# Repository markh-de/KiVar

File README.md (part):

# KiVar − Multi-Scope PCB Assembly Variants for KiCad

KiVar is a tool for **KiCad PCB Assembly Variant and Micro-Variant selection**, provided as platform-independent

 * **KiCad Plugin** and
 * **Command Line Application**.

PCB component variation rules for multiple independent design scopes are defined in component (i.e. symbol or footprint) fields.  This allows for the complete low-level variation configuration to be contained in the schematic and board files without requiring external data outside the native KiCad design.

In addition, Variant Definition Tables (KiCad-independent CSV format) can optionally be used to summarize the configuration of these low-level scopes in classic flat variants, which can then be switched between.

> [!NOTE]
> While KiCad 10 introduces native assembly variant support, KiVar's concept of **multiple independent Aspects** (or _Micro-Variants_) goes beyond a single flat variant switch.  Each Aspect represents its own variation scope &ndash; such as LED current, boot source, I²C address, or output voltage &ndash; and each can be set independently or grouped into named Variants.  This multi-scope approach continues to offer unique flexibility that complements or exceeds what common EDA variants provide.

## Featured at KiCon Europe 2024

For a presentation of the **concepts** and **features** of KiVar, including a **short tutorial**, you can watch the talk ["**Managing PCB Assembly Variants with KiVar**"](https://youtu.be/SpXH380KWUA), which was recorded at KiCon Europe 2024 in Bochum, Germany.

The presentation **slides** including the embedded screencast videos can be downloaded from the [pretalx page](https://pretalx.kicad.org/kicon-europe-2024/talk/QMYVCL/).

> [!NOTE]
> The presentation covered KiVar 0.4.0, which did not yet support flat variants (added in 0.5.0).

Many thanks to Seth for the invitation.

## Features

KiVar assigns PCB component **values**, **field content**, **attributes** (such as _Do not populate_, _Not in position files_ or _Not in BoM_) and **features** (such as _individual 3D model visibility_ or _solder paste application_) according to variation rules specified in footprint fields.  When applying those rules, components are modified **in place**, allowing for immediate update of the PCB design as well as the 3D view and enabling compatibility with _any_ exporter.

Back-propagation of modified component data from the PCB to the schematic can be done in an extra step.

## What to Expect

### KiCad Plugin

Example selection dialog of the **KiVar Plugin for KiCad**:

### Command Line Interface Application

Example usage of the **KiVar Command Line Interface app**:

```
$ kivar list --selection kivar-demo.kicad_pcb 
~: 'Series 1000' 'Series 3000 Basic' ['Series 3000 Pro'] 'Series 5000 Basic' 'Series 5000 Pro'
BOOT_SRC~: EMMC JP NAND [SD]
IOEXP_TYPE/ADDR~: 9535/0x20 [9535/0x24] 9539/0x74
EEPROM_ADDR~: [0x54] 0x55
I_LED_MA~: 10 20 30 40 50 60 70 80 90 [100] 110 120 130 140 150 JP
ISL91127~: [IRAZ] IRNZ
UVLO_LO/HI: 2.41V/3.40V [3.15V/3.57V]
VOUT: 1.2V [1.8V] 2.5V 3.3V

$ kivar set --variant 'Series 5000 Pro' --verbose kivar-demo.kicad_pcb 
Changes (19):
    Change R1 'Do not populate' from 'true' to 'false' (EEPROM_ADDR=0x55).
    Change R1 'Exclude from bill of materials' from 'true' to 'false' (EEPROM_ADDR=0x55).
    Change R1 'Exclude from position files' from 'true' to 'false' (EEPROM_ADDR=0x55).
    Change R2 'Do not populate' from 'false' to 'true' (EEPROM_ADDR=0x55).
    Change R2 'Exclude from bill of materials' from 'false' to 'true' (EEPROM_ADDR=0x55).
    Change R2 'Exclude from position files' from 'false' to 'true' (EEPROM_ADDR=0x55).
    Change R21 field 'VarID' from 'A' to 'B' (I_LED_MA=110).
    Change R30 'Do not populate' from 'true' to 'false' (I_LED_MA=110).
    Change R30 'Exclude from bill of materials' from 'true' to 'false' (I_LED_MA=110).
    Change R30 'Exclude from position files' from 'true' to 'false' (I_LED_MA=110).
    Change U1 field 'I2C Address' from '0x54' to '0x55' (EEPROM_ADDR=0x55).
    Change U1 field 'VarID' from '54' to '55' (EEPROM_ADDR=0x55).
    Change U4 value from 'TCA9535PWR' to 'TCA9539PWR' (IOEXP_TYPE/ADDR=9539/0x74).
    Change U4 visibility of 3D model #1 from 'true' to 'false' (IOEXP_TYPE/ADDR=9539/0x74).
    Change U4 visibility of 3D model #2 from 'false' to 'true' (IOEXP_TYPE/ADDR=9539/0x74).
    Change U4 field 'I2C Address' from '0x24' to '0x74' (IOEXP_TYPE/ADDR=9539/0x74).
    Change U4 field 'VarID' from '24' to '74' (IOEXP_TYPE/ADDR=9539/0x74).
    Change U4 field 'Datasheet' from 'http://www.ti.com/lit/ds/symlink/tca9535.pdf' to 'http://www.ti.com/lit/ds/symlink/tca9539.pdf' (IOEXP_TYPE/ADDR=9539/0x74).
    Change U4 field 'MPN' from 'TCA9535PWR' to 'TCA9539PWR' (IOEXP_TYPE/ADDR=9539/0x74).
Board saved to file "kivar-demo.kicad_pcb".

$ kivar list --selection kivar-demo.kicad_pcb 
~: 'Series 1000' 'Series 3000 Basic' 'Series 3000 Pro' 'Series 5000 Basic' ['Series 5000 Pro']
BOOT_SRC~: EMMC JP NAND [SD]
IOEXP_TYPE/ADDR~: 9535/0x20 9535/0x24 [9539/0x74]
EEPROM_ADDR~: 0x54 [0x55]
I_LED_MA~: 10 20 30 40 50 60 70 80 90 100 [110] 120 130 140 150 JP
ISL91127~: [IRAZ] IRNZ
UVLO_LO/HI: 2.41V/3.40V [3.15V/3.57V]
VOUT: 1.2V [1.8V] 2.5V 3.3V

$ kivar check kivar-demo.kicad_pcb 
Check passed.  Matching variant and choices found for complete set of 7 aspect(s).

$ kivar state --query EEPROM_ADDR --query BOOT_SRC kivar-demo.kicad_pcb 
0x55
SD
```

The KiVar CLI application provides support for

 * setting,
 * querying,
 * listing and
 * analyzing

low-level and high-level variant data and current settings of a PCB.  It can also be used in Continuous Integration services.

## Concepts

Key concepts of KiVar are:

 * Designs may contain **multiple** independent **aspect scopes** (micro-variants).
 * Variation rules are **fully contained** in component fields of native design files (no external configuration files involved) and **portable** (i.e. copying components to another design keeps their variation specification intact).
 * Component values, fields, attributes and features are modified **in place** with immediate effect, enabling compatibility with all exporters that work on the actual component data.
 * **No external state information** is stored; currently matching variation choices are detected automatically.
 * Optional external **variant** definition table in independent file format (CSV) enables switching of aspect groups based on a single variant name.

## Supported KiCad Versions

KiCad Release Series | Compatible KiVar Releases
-------------------- | -------------------------
7.x                  | 0.0.1 &ndash; 0.1.2
8.x                  | 0.2.0 &ndash; _latest_
9.x                  | 0.4.2 &ndash; _latest_
10.x                 | 0.5.4 &ndash; _latest_

> [!NOTE]
> KiCad 10 introduces native assembly variant support.  However, KiVar's **multi-scope Aspect model** provides flexibility beyond KiCad's built-in single design-scope variant selection.

KiVar currently (still) uses the SWIG-based Python bindings of pcbnew (KiCad PCB Editor).

## Installation

> [!NOTE]
> The KiCad Plugin and the CLI app can be installed independently of each other.  As the KiCad Plugin does not have external module dependencies, it does not require the CLI package to be installed.

### KiVar Plugin

The recommended plugin installation method is to use KiCad's integrated **Plugin and Content Manager**.  KiVar is included in the **official PCM repository**, allowing a smooth and safe installation and update experience.

Required steps:

1. Start the _Plugin and Content Manager_ from the KiCad main window.
2. Find _KiVar_ in the **Plugins** section.
3. Mark it for installation and apply the pending changes.
4. The _KiVar_ plugin icon should now appear in the PCB Editor (pcbnew) toolbar.

### KiVar Command Line Application

To install the latest KiVar CLI app directly from the official **KiVar PyPI repository**, follow the instructions below depending on your operating system.

#### Installation on Linux

For conveniently installing the KiVar CLI app inside a dedicated Virtual Environment, it is recommended to use `pipx`.  Install it, if required, depending on your type of Linux distribution.  With `pipx` in place, open a shell and run:

```
pipx install --system-site-packages kivar
```

This will install the KiVar CLI app in a location available in your search path.  The name of the executable is `kivar`.

To check that the installation was successful and that the correct `pcbnew` module version is used, run:

```
kivar --version
```

#### Installation on Windows

On Windows systems, KiCad ships with its own Python distribution included.  It is important to **use the KiCad-provided Python interpreter** for installing the KiVar CLI app.

To install the `kivar.exe` executable, open a `cmd.exe` shell and run:

```
"%ProgramFiles%\KiCad\9.0\bin\python.exe" -m pip install --user kivar
```

> [!NOTE]
> The above command assumes that KiCad version 9.0 is used.  Please adapt the version part (`9.0`) of the command, if required.

If you don't happen to have the app installation directory already listed in your `PATH` variable, then `pip` will print a warning including the actual installation directory:

```
WARNING: The script kivar.exe is installed in '...' which is not on PATH.
```

This message includes the location of the directory in which the `kivar.exe` executable is installed.

You will need to run `kivar` from this exact location.  If desired, you can add the installation directory to your `PATH` variable (as suggested by `pip`), or use any other preferred method of making the executable callable from any working directory.

To check that the installation was successful and that the correct `pcbnew` module version is used, run:

```
"%USERPROFILE%\Documents\KiCad\9.0\3rdparty\Python311\Scripts\kivar" --version
```

> [!NOTE]
> The path used in the above command may differ on your system.  If in doubt, use the directory printed in the `pip` installation warning.  If no such warning appeared, you might be able to simply use `kivar --version` (without path specifier).

#### Installation on macOS

On macOS systems, KiCad ships with its own Python distribution included.  It is important to **use the KiCad-provided Python interpreter** for installing the KiVar CLI app.

To install the `kivar` executable, open a shell and run:

```
"/Applications/KiCad/KiCad.app/Contents/Frameworks/Python.framework/Versions/Current/bin/python3" -m pip install --user kivar
```

If you don't happen to have the app installation directory already listed in your `PATH` variable, then `pip` will print a warning including the actual installation directory:

```
WARNING: The script kivar is installed in '...' which is not on PATH.
```

To be able to call `kivar` from _any_ working directory without using the executable's full path, run the following commands to create a symlink in your `~/.local/bin` directory (which should be part of `PATH`).  The actual Python version part (`3.9` here) may vary, depending on the KiCad-included Python version.

```
mkdir -p "$HOME/.local/bin"
ln -s "$HOME/Library/Python/3.9/bin/kivar" "$HOME/.local/bin/kivar"
```

> [!NOTE]
> The path used in the above command may differ on your system.  If in doubt, use the directory printed in the `pip` installation warning.

To check that the installation was successful and that the correct `pcbnew` module version is used, run:

```
kivar --version
```

## Usage

> [!TIP]
> This manual may seem very formal and complicated, especially to new users.  To get a first impression how KiVar works, it is highly recommended to watch the live presentation ["**Managing PCB Assembly Variants with KiVar**"](https://youtu.be/SpXH380KWUA) and have a look at the **[usage examples](#usage-examples)** as well as the **[demo project](demo/)** (from which the examples are taken).

> [!IMPORTANT]
> This manual refers to the **0.5.x** series of KiVar.  If you are still using an older version, please consider [updating](#installation) KiVar and [migrating](#migrate) your variation rules.

The process of writing and assigning rules to components (i.e. symbols and footprints) is done manually using simple text expressions.

In addition, groups of configurations can be conveniently managed in tables (CSV files).

Once all relevant components are equipped with their variation rules and variant tables are set up (optionally), KiVar allows the selection of variation choices using either an easy-to-use dialog interface (when using the KiCad Plugin) or a command-line interface (when using the CLI app) and takes care of the automatic analysis and assignment of the corresponding component values, fields, attributes and features.

The following sections describe the process of configuring your schematic or board, your variant table (if desired) and &ndash; after that &ndash; selecting a variation configuration from the previously configured variation choices.  Examples are provided where appropriate.

### Component Variation Setup

While it is recommended to define variation rules in the schematic (i.e. in symbol fields) and propagate them to the board, it is also possible to define those rules directly in the board (i.e. in footprint fields) and propagate them back to the schematic.  Either way, in order for KiVar to utilize the variation rules, they must be present in the footprint fields, as KiVar uses the _pcbnew_ API wrapper and can therefore only operate on the board (not schematic) data, which must then be [propagated back to the schematic](#updating-the-schematic).

> [!TIP]
> If you are already experienced with writing variation rules for **older KiVar versions**, it is highly recommended to read the **[KiVar Migration Guide](#migrate)**, which covers the most important changes introduced with newer KiVar releases.

#### Definition of Terms

Whenever specific terms appear capitalized in this document, the following definitions apply:

 * **Aspect:**  
   A scope (or dimension) of variation changes, which are defined by _Choices_ (see below).  One PCB design can refer to multiple Aspects.  Each component that makes use of KiVar variations must refer to _exactly one_ [Aspect Identifier](#aspect-identifier).  
   For example, an Aspect can be the I²C address of an EEPROM IC, using an identifier such as `EEPROM_I2C_ADDR`.
 
 * **Choice:**  
   A state of an _Aspect_.  Defined with a set of [Content](#content-specifiers) (component values or component field values) and/or [Properties](#property-specifiers) to be assigned to specific components.  A Choice is _always_ related to a specific _Aspect_ and only valid in its context.  
   For example, possible Choices for the I²C address Aspect could be `0x50`, `0x51`, `0x52`, `0x53`.

 * **Configuration:**  
   A fully defined selection of _specific_ _Choices_ for _all_ available _Aspects_.  In other words, one specific board assembly variant state.  
   An example is shown in the following section.

 * **Record:**  
   An entry in a KiVar-specific custom field of a component (symbol or footprint) to be interpreted by the KiVar rule processor.

 * **Assignment:**  
   A group of one or more Records containing [Choice Expressions](#choice-expressions) to assign a set of data to the same Assignment target (e.g. the [component itself](#component-scope), or an existing [custom field of the component](#field-scope)).

 * **Variant:**  
   A set of _Choices_ applying to a selected set of _Aspects_ (so-called _Bound Aspects_ &ndash; in contrast to _Free Aspects_, which can be modified independently of the selected Variant).  
   The use of Variants is optional.  If used, Variants are [configured independently](#top-level-variants) "on top" of the existing _Aspect_ configuration.

#### Variants

##### Multi-Scope Concept

A central point of KiVar's concepts is that one design can use any number of **independent** Aspect scopes and each scope can be switched to a specific Choice (Aspect state).

This is KiVar's key differentiator from classic flat variant systems &ndash; including KiCad 10's native variant support.  Instead of a single monolithic variant switch that controls all component changes at once, KiVar treats each variation dimension (e.g. output voltage, boot source, LED current, I²C address) as its own independently switchable **Aspect**.  Each Aspect has its own set of **Choices** (Micro-Variants), which can be selected freely and in any combination.  This makes it possible to represent a much larger configuration space with far fewer explicitly defined Variants.

##### Flat Variants

Most EDA tools offer a "flat variant" model.  Which makes sense, because in real-world projects, it is often desired to have a **single global** (i.e. top-level) switch to choose between assembly options, for example to switch between product models or revisions that always combine a specific set of assembly Choices.

##### Mixed Approach

KiVar uses a mixed approach, combining the benefits of both concepts:

The definition of Variants makes it possible to work with a single switch, while the configuration of the individual Variants is still very convenient, as it is only necessary to **switch between Choices for Bound Aspects, not between the full set of component values and attribute data**.  This additional layer of abstraction keeps Variant definitions very simple and readable.

In addition to a single Variant switch, KiVar also allows having so-called _Free Aspects_, i.e. scopes that are not modified when selecting a specific Variant.  So even after switching the main Variant, it is still possible to have a few independent switches for further assembly options, if desired.

##### Division of Resposibilities

Component value and attributes are configured in _low-level_ Aspect definitions directly in the native KiCad design files, while _top-level_ Variants are configured independently in an external table.

This makes it possible to divide the administration of each of these parts between different departments or editors, providing a _development_ and _management_ view:

While low-level Aspects can be defined by the KiCad hardware _developers_ during design, the project _manager_ can be in charge of defining model/series/product feature configurations by mapping Aspect Choices to specific Variants.  For the _management_ view, it is not even required to use an installation of KiCad (or KiVar).  A simple spreadsheet editor is sufficient to manage the Variants table.

##### Specification

Details about the specification of Variants can be found later in this manual in the [Top-Level Variants section](#top-level-variants).

#### Relation of Aspects and Choices

Each component that uses KiVar variation rules must bind to _exactly one_ variation **Aspect** to which all specified variation **Choices** for that component will then relate to.

> [!IMPORTANT]
> There may exist _multiple_ Aspects per design, and for each Aspect there may exist _multiple_ Choices.  
> One component must relate to a _single_ Aspect, but may relate to an _unlimited number_ of Choices for that Aspect.  
> Multiple components may (and usually will) refer to the same Aspects and Choices.

_Example:_

 * Design
   * Aspect `EEPROM_I2C_ADDR`
     * Choice `0x50`
     * Choice `0x51`
     * Choice `0x52`
     * Choice `0x53`
  
   * Aspect `BOOT_SRC`
     * Choice `EMMC`
     * Choice `SDCARD`
     * Choice `NAND`
  
   * Aspect `VIO_LEVEL`
     * Choice `1.8V`
     * Choice `2.5V`
     * Choice `3.3V`

One possible resulting example _Configuration_ for this design:

`EEPROM_I2C_ADDR=0x52 BOOT_SRC=NAND VIO_LEVEL=1.8V`

KiVar computes possible sets of Aspect and Choice definitions internally by checking each component's field data for KiVar [Records](#records) and the [Assignments](#assignments) resulting from them.  The structure and syntax of the expressions used in such Records are described in the following sections.

#### Overriding KiVar Record Keywords

By default, KiVar uses the keywords `Var` and `Aspect` in component fields to identify variation rules and Aspect Identifiers.

**You can override these default keywords** by defining the KiCad project text variables `KIVAR_KEYWORD_VAR` and `KIVAR_KEYWORD_ASPECT`, respectively.

For example, to use `Scope` instead of `Aspect`, set `KIVAR_KEYWORD_ASPECT` = `Scope` in your project's text variables.

This allows you to adapt KiVar to your own naming conventions or to avoid conflicts with other tools.  However, using custom keywords may make your variation rules less portable.

#### Records

The text expressions that describe the variation rules are noted as **Record**s, i.e. as custom field entries with each field's name containing the keyword `Var` in one of [several forms](#record-formats).

Records must appear in the component they relate to.

A usual Record contains the following elements:

 * [Assignment](#assignments) Target information: _implicit, depending on the [Assignment Scope](#assignment-scopes)_
 * [Choice Expression(s)](#choice-expressions): _one or more, depending on the [Record Format](#record-formats)_
   * [Choice Identifier List](#choice-identifier-lists): _list of affected Choice names_
   * [Choice Argument(s)](#choice-arguments): _data to be assigned to the affected Choices_
     * [Content Specifier(s)](#content-specifiers): _provide data to be used as component value or custom field value_
     * [Property Specifier(s)](#property-specifiers): _provide settings to switch component attributes or footprint features_

There is a special Aspect Specifier Record type, discussed in the [corresponding section](#aspect-identifier).

Records can use various notations, depending on their [Format](#record-formats).  Details are described in the following sections.

> [!NOTE]
> The default field keywords `Var` and `Aspect` can be changed per project.  
> See [Overriding KiVar Record Keywords](#overriding-kivar-record-keywords) for details.

#### Assignments

Each Record addresses a specific target that the contained rule expressions refer to.  A group of one or more Records with the same target form an **Assignment**.

Possibe Assignment targets are:

 * the component's **value**,
 * one of the component's (custom) **fields**,
 * a component **attribute** and/or
 * a component **feature** (e.g. solder paste application, 3D representation).

#### Choice Expressions

Depending on the used [Format](#record-formats), each Record can carry either a single or multiple **Choice Expression**s.

Each Choice Expression specifies

 * for which [Choice Identifiers](#choice-identifiers) to assign
 * which data to the Record's [Assignment](#assignments) target.

For each Choice Expression, this data is passed via the

 * [Choice Identifier List](#choice-identifier-lists) and
 * [Choice Arguments](#choice-arguments).

#### Choice Arguments

The actual data to be assigned to the Choices passed as [Choice Identifier List](#choice-identifier-lists) is expressed in the **Choice Argument**s.

These Choice Arguments are a list of _space_-separated specifiers used to declare the data to be assigned to the [Assignment](#assignments) Target.

Each _Choice Argument_ inside the _Choice Argument List_ can be of one of two possible types:

 * a [**Content** Specifier](#content-specifiers) to assign a component _value_ or a specific _custom field value_, or
 * a [**Property** Specifier](#property-specifiers), e.g. to mark a component _(un)fitted_, _(not) in BoM_, _(not) in position files_ or change a dedicated footprint feature.

Argument types are distinguished by their **first (unescaped) character** and will be explained in more detail in the following sub-sections.

##### Content Specifiers

###### Purpose

One or more **Content Specifiers** can be used to form a string to be assigned to the component value or to any component custom field (such as _Manufacturer_, _MPN_, ...).

###### Syntax

Each argument beginning with a character _other than_ `-` and `+` is interpreted as a **Content Specifier**.

There may exist multiple Content Specifiers in each [Choice Argument](#choice-arguments) List.  Their values will be concatenated with one ` ` (space) character as separator to form the resulting Content string.  However, each [Assignment](#assignments) may have a maximum of _one_ resulting Content specified.  For example: `Choice1("hello world"   foo bar)` will result in `Choice1` to be assigned the content `hello world foo bar`, but multiple Content Assignments to the same [Choice Identifier](#choice-identifiers), such as `Choice1("hello world") Choice1(foo bar)`, are invalid.  This restriction is due to the fact that [Records](#records) can be provided in different [Formats](#record-formats) and there is no guaranteed processing (concatenation) order.

###### Evaluation

All Content Specifiers inside the Choice Arguments are evaluated from left to right and concatenated with one space character between each argument to form the final content string to be assigned when the corresponding Choice is selected.

> [!NOTE]
> As arguments can be separated by _any_ number of space characters, each separation will result in a single space character in the final content, no matter how many spaces were used for the argument separation originally (similar to HTML).  For strings that shall be assigned in a verbatim way (such as a URL), it is highly recommended to use [quoting techniques](#quoting-and-escaping).

###### Examples

The Content Specifiers in the following input Choice Argument Lists will result in the following Content strings:

Choice Argument List input | Resulting Content string | Explanation
-------------------------- | ------------------------ | -----------
`100nF`                    | `100nF`                  | Simple single arguments can be noted without [escaping or quoting](#quoting-and-escaping) as long as they don't contain certain special characters (discussed later).
`470µF 10%`                | `470µF 10%`              | Uncritical text, no verbatim adoption of the arguments required.
`470µF   10%`              | `470µF 10%`              | Multiple separator characters will be converted to a single separator. As the text is uncritical, this conversion may even be desired.
`'https://kivar.markh.de/ds/abc123.pdf'` | `https://kivar.markh.de/ds/abc123.pdf` | Strings to be used verbatim should always be enclosed in [quote](#quoting-and-escaping) characters.
`'abc   def ' 123   456`   | `abc   def  123 456`     | Mixed type of quoted and unquoted representation.  Note how the trailing space after `def` remains contained in the result.
`abc "def 'ghi' jkl" mno`  | `abc def 'ghi' jkl mno`  | Outer double quotes encapsulate inner single quotes, which are part of the verbatim string.
`abc 'def "ghi" jkl' mno`  | `abc def "ghi" jkl mno`  | Outer single quotes encapsulate inner double quotes, which are part of the verbatim string.
`abc \d\e\f\ \ ghi\'jkl\\mno` | `abc def  ghi'jkl\mno` | [Escaping](#quoting-and-escaping) (prepending a backslash) ensures that the following character is interpreted verbatim, not as a special character.  To create a backslash (the escape character) string, use a double backslash (i.e. escape the backslash).
`\+10% \-5% \-12V \+5V`    | `+10% -5% -12V +5V`      | If the first character of a Content Specifier is a `-` or `+`, the corresponding Choice Argument must be prepended with a backslash (`\`) character or be part of a verbatim string (see next example).
`"+10%" '-5%' "-"12V '+'5V` | `+10% -5% -12V +5V`     | If the first character of a Content Specifier is a `-` or `+`, the corresponding Choice Argument must be part of a verbatim string or be prepended with a backslash (`\`) character (see previous example).

##### Property Specifiers

###### Purpose

KiVar provides a set of boolean component _Properties_ that allow controlling the component attributes

 * **Do not Populate**,
 * **Not in Position Files**, and
 * **Not in BoM**
 
as well as component features, such as

 * **Individual 3D Model Visibility** and
 * **Solder Paste Application**.

###### Syntax

Each argument beginning with a `-` or `+` is interpreted as a **Property Specifier**, which is a combination of **Property Modifiers** and **Property Identifiers**.

Each Property Specifier must start with a _Property Modifier_, defining the boolean state (_true_ or _false_, represented by `+` or `-`, respectively) to be assigned to the Properties subsequently specified by their corresponding _Property Identifiers_.

###### Evaluation

All Property Specifiers inside a [Choice Argument List](#choice-arguments) are evaluated from left to right, resulting in a set of defined boolean Property states for the corresponding component and Choice.  Properties _not_ defined in _any_ of the component's Choices are kept in their original state.

###### Attribute Properties

The following Properties allow modification of component _attributes_:

 * **Fit** (Property identifier `f`).  
   This Property specifies whether a component shall be fitted (Property state _true_) or unfitted (Property state _false_).  This Property is linked to the pcbnew footprint attribute _Do not populate_ with inverted polarity.
 * **Pos** (Property identifier `p`).  
   This Property specifies whether a component shall be included in the component placement/position files (Property state _true_) or excluded (Property state _false_).  This Property is linked to the pcbnew footprint attribute _Not in Position Files_ with inverted polarity.
 * **Bom** (Property identifier `b`).  
   This Property specifies whether a component shall be included in the Bill of Materials (Property state _true_) or excluded (Property state _false_).  This Property is linked to the pcbnew footprint attribute _Not in BoM_ with inverted polarity.

###### Feature Properties

Additionally, the following Properties allow controlling footprint _features_:

 * **Model** (Property identifier `mN`, with `N` being an integer number).  
   This Property controls the visibility of each individual 3D model of the corresponding component footprint to either visible (Property state _true_) or invisible (Property state _false_).  An integer number must be provided directly following the first character of the Property identifier, representing the index of the model to be shown or hidden.  The index starts at 1.
 * **Solder** (Property identifier `s`).  
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
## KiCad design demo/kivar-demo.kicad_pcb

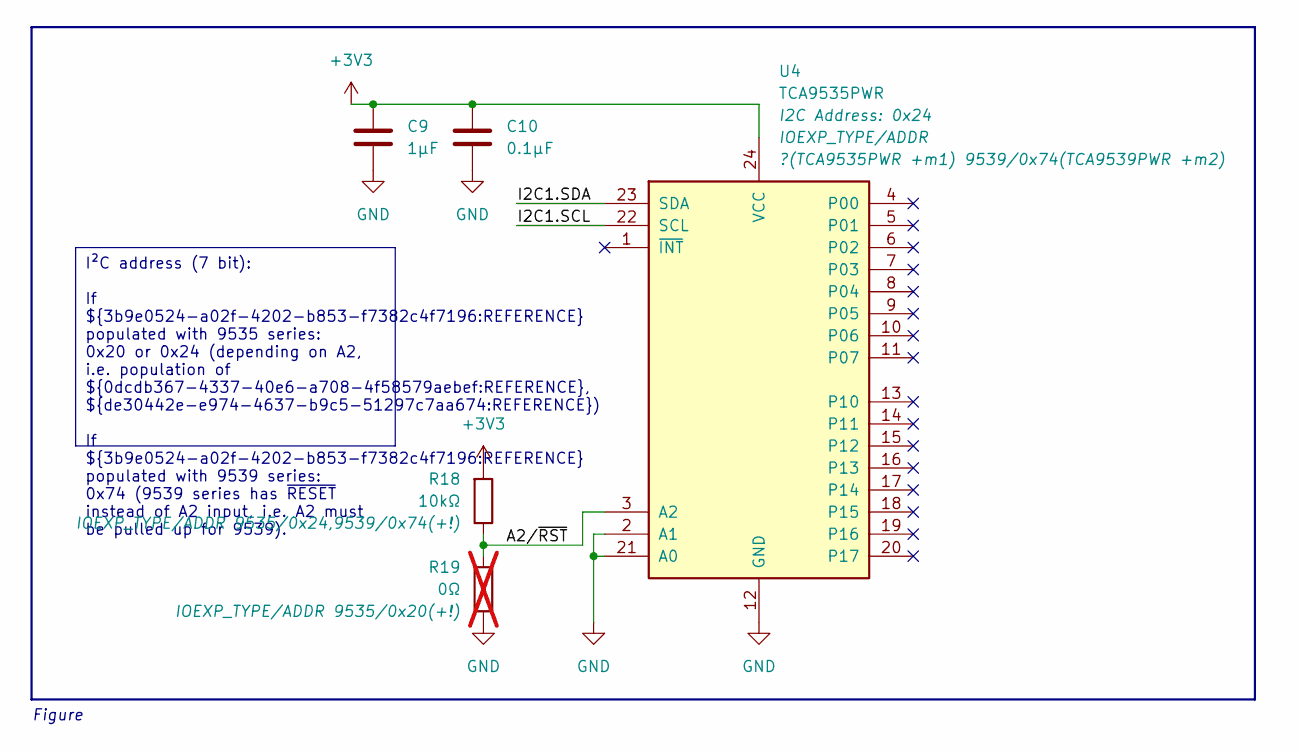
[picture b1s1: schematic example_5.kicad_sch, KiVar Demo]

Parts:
C9: 1µF; C_0603_1608Metric
C10: 0.1µF; C_0402_1005Metric
R18: 10kΩ; R_0402_1005Metric
R19: 0Ω; R_0402_1005Metric; not fitted
U4: TCA9535PWR; TSSOP-24_4.4x7.8mm_P0.65mm; MPN TCA9535PWR

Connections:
+3V3: C9.1, C10.1, R18.2, U4.24 (VCC); also elsewhere on the board
/Example 5: IC Type and Address Selection/A2/~RST: R18.1, R19.2, U4.3 (A2)
/Example 5: IC Type and Address Selection/I2C1.SCL: U4.22 (SCL)
/Example 5: IC Type and Address Selection/I2C1.SDA: U4.23 (SDA)
GND: C9.2, C10.2, R19.1, U4.2 (A1), U4.12 (GND), U4.21 (A0); also elsewhere on the board

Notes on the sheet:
I²C address (7 bit): If ${3b9e0524-a02f-4202-b853-f7382c4f7196:REFERENCE} populated with 9535 series: 0x20 or 0x24 (depending on A2, i.e. population of ${0dcdb367-4337-40e6-a708-4f58579aebef:REFERENCE}, ${de30442e-e974-4637-b9c5-51297c7aa674:REFERENCE}) If ${3b9e0524-a02f-4202-b853-f7382c4f7196:REF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
Figure

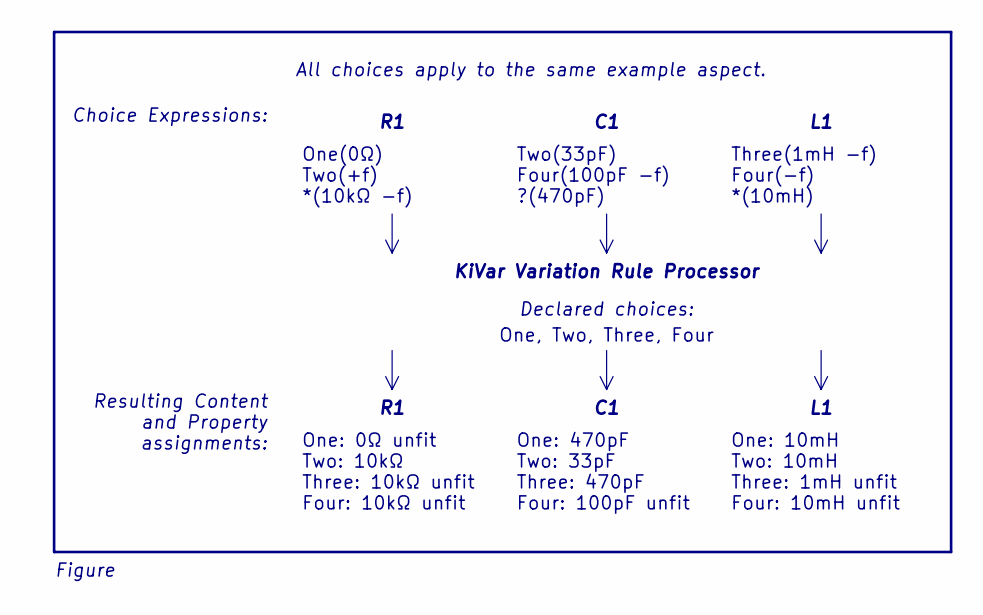
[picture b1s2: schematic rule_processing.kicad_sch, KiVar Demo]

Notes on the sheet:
KiVar Variation Rule Processor
One: 10mH Two: 10mH Three: 1mH unfit Four: 10mH unfit
Two(33pF) Four(100pF -f) ?(470pF)
One: 470pF Two: 33pF Three: 470pF Four: 100pF unfit
Three(1mH -f) Four(-f) *(10mH)
Figure
One, Two, Three, Four
One: 0Ω unfit Two: 10kΩ Three: 10kΩ unfit Four: 10kΩ unfit
All choices apply to the same example aspect.
Resulting Content and Property assignments:
Choice Expressions:
One(0Ω) Two(+f) *(10kΩ -f)
Declared choices:

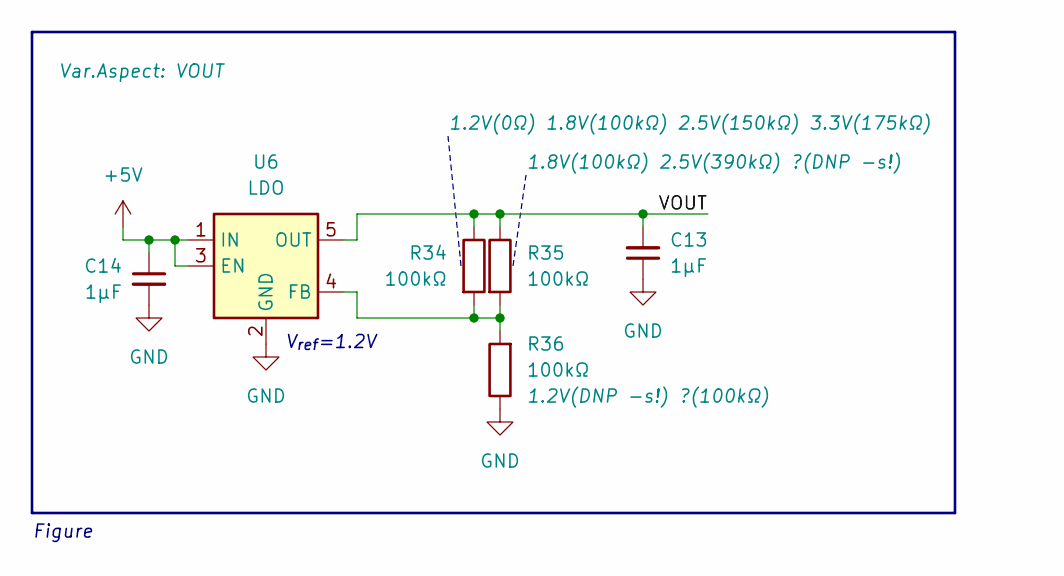
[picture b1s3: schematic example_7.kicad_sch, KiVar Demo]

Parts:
C13, C14: 1µF; C_0603_1608Metric
R34, R35, R36: 100kΩ; R_0402_1005Metric_Pad0.72x0.64mm_HandSolder
U6: LDO; SOT-23-5

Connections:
+5V: C14.1, U6.1 (IN), U6.3 (EN)
/Example 7: LDO Output Voltage Selection/VOUT: C13.2, R34.1, R35.1, U6.5 (OUT)
GND: C13.1, C14.2, R36.1, U6.2 (GND); also elsewhere on the board
unnamed: R34.2, R35.2, R36.2, U6.4 (FB)

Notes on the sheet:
V_{ref}=1.2V
Figure

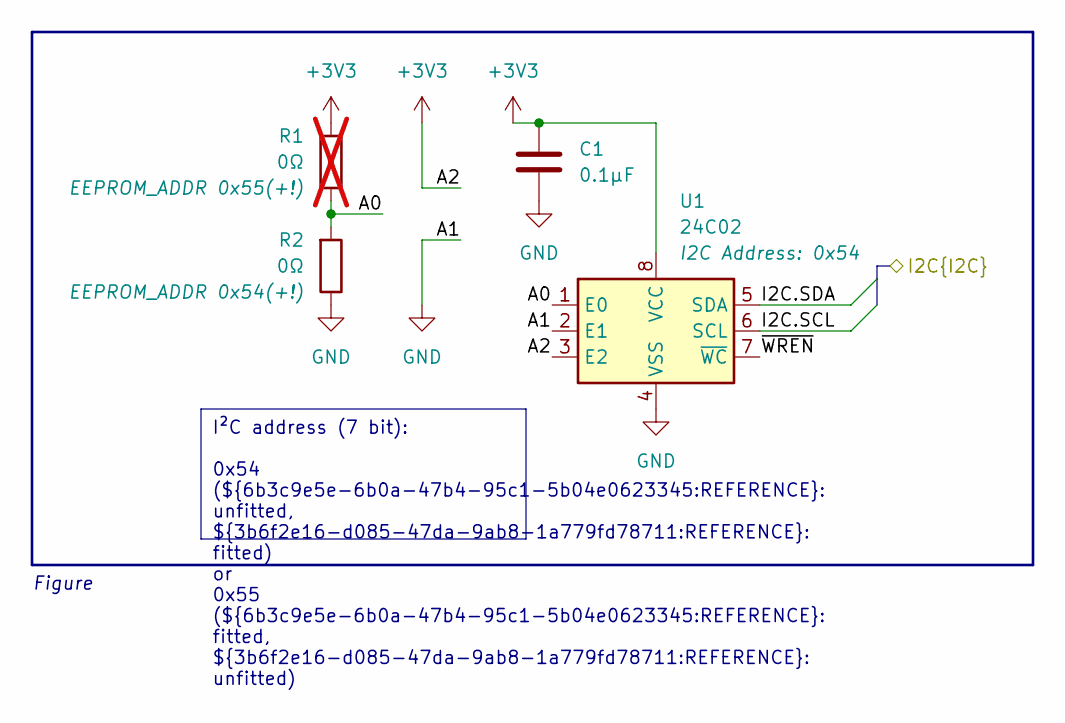
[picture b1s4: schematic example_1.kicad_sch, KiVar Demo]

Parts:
C1: 0.1µF; C_0402_1005Metric
R1: 0Ω; R_0402_1005Metric; not fitted
R2: 0Ω; R_0402_1005Metric
U1: 24C02; TSSOP-8_4.4x3mm_P0.65mm

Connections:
+3V3: C1.1, R1.2, U1.3 (E2), U1.8 (VCC); also elsewhere on the board
/Example 1: I²C Device Address Selection/A0: R1.1, R2.2, U1.1 (E0)
/Example 1: I²C Device Address Selection/I2C.SCL: U1.6 (SCL)
/Example 1: I²C Device Address Selection/I2C.SDA: U1.5 (SDA)
/Example 1: I²C Device Address Selection/~WREN: U1.7 (~WC)
GND: C1.2, R2.1, U1.2 (E1), U1.4 (VSS); also elsewhere on the board

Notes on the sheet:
I²C address (7 bit): 0x54 (${6b3c9e5e-6b0a-47b4-95c1-5b04e0623345:REFERENCE}: unfitted, ${3b6f2e16-d085-47da-9ab8-1a779fd78711:REFERENCE}: fitted) or 0x55 (${6b3c9e5e-6b0a-47b4-95c1-5b04e0623345:REFERENCE}: fitted, ${3b6f2e16-d085-47da-9ab8-1a779fd78711:REFERENCE}: unfitted)
Figure

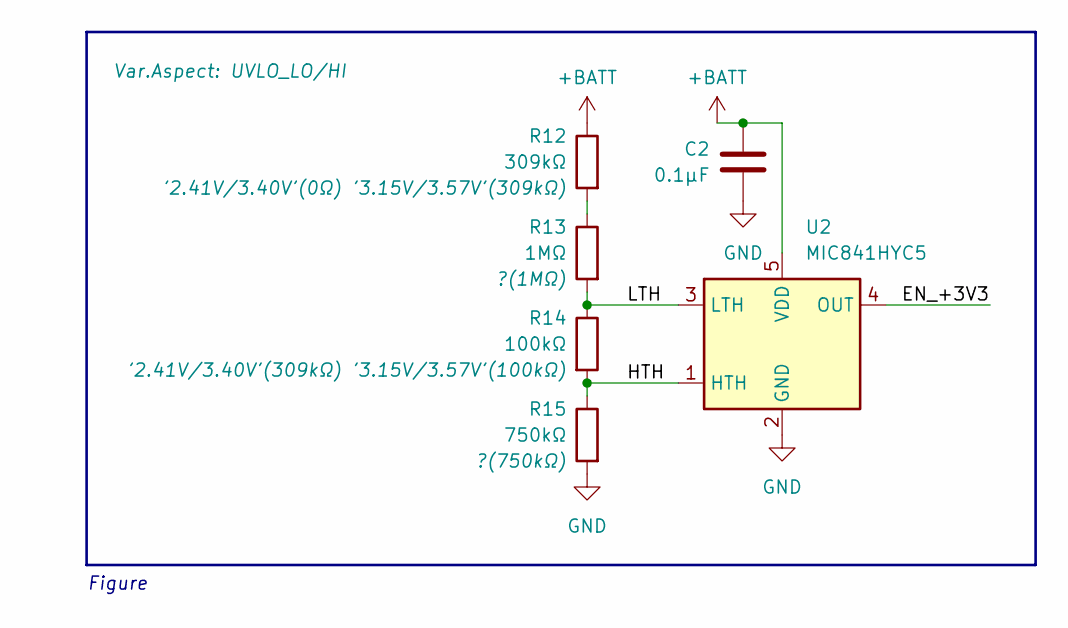
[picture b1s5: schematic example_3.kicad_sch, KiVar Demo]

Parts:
C2: 0.1µF; C_0402_1005Metric
R12: 309kΩ; R_0402_1005Metric
R13: 1MΩ; R_0402_1005Metric
R14: 100kΩ; R_0402_1005Metric
R15: 750kΩ; R_0402_1005Metric
U2: MIC841HYC5; SOT-353_SC-70-5

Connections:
+BATT: C2.1, R12.1, U2.5 (VDD); also elsewhere on the board
/Example 3: Undervoltage Trip Points/EN_+3V3: U2.4 (OUT)
/Example 3: Undervoltage Trip Points/HTH: R14.2, R15.1, U2.1 (HTH)
/Example 3: Undervoltage Trip Points/LTH: R13.2, R14.1, U2.3 (LTH)
GND: C2.2, R15.2, U2.2 (GND); also elsewhere on the board
unnamed: R12.2, R13.1

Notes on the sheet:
Figure

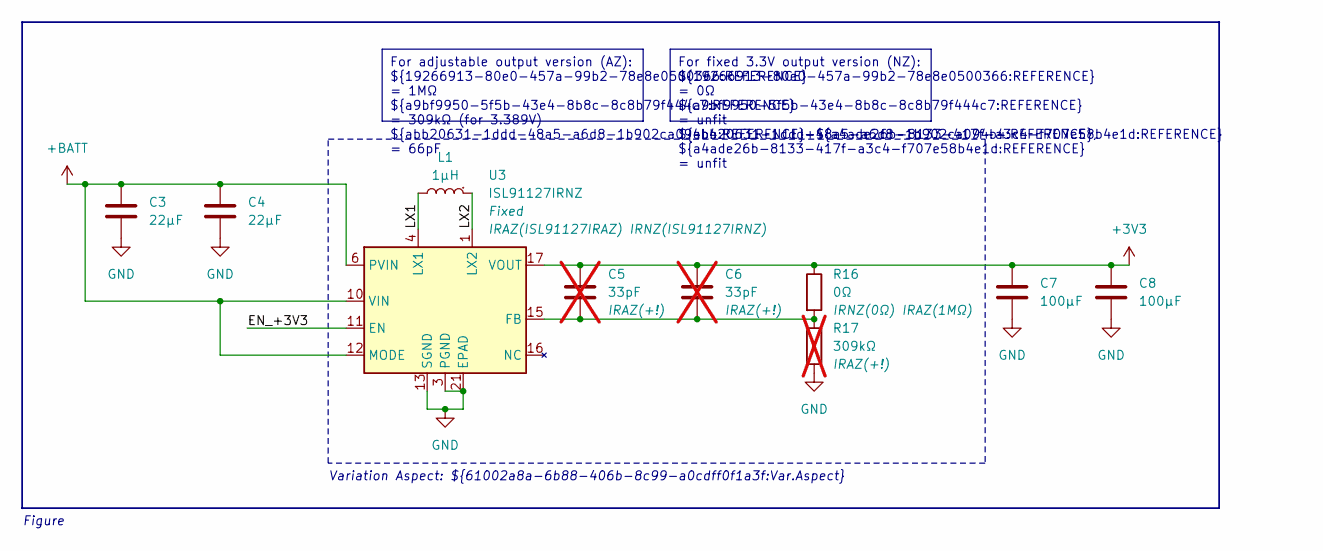
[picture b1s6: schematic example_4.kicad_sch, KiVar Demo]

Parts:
C3, C4: 22µF; C_1206_3216Metric
C5, C6: 33pF; C_0402_1005Metric; not fitted
C7, C8: 100µF; C_1210_3225Metric
L1: 1µH; L_Coilcraft_XAL4030-XXX
R16: 0Ω; R_0402_1005Metric
R17: 309kΩ; R_0402_1005Metric; not fitted
U3: ISL91127IRNZ; QFN-20-1EP_4x4mm_P0.5mm_EP2.5x2.5mm; MPN ISL91127IRNZ-T7A

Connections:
+3V3: C5.1, C6.1, C7.1, C8.1, R16.1, U3.17 (VOUT), U3.18 (VOUT), U3.19 (VOUT), U3.20 (VOUT); also elsewhere on the board
+BATT: C3.1, C4.1, U3.6 (PVIN), U3.7 (PVIN), U3.8 (PVIN), U3.9 (PVIN), U3.10 (VIN), U3.12 (MODE); also elsewhere on the board
/Example 4: IC Variant Selection/EN_+3V3: U3.11 (EN)
/Example 4: IC Variant Selection/LX1: L1.2, U3.4 (LX1), U3.5 (LX1)
/Example 4: IC Variant Selection/LX2: L1.1, U3.1 (LX2), U3.2 (LX2)
GND: C3.2, C4.2, C7.2, C8.2, R17.2, U3.3 (PGND), U3.13 (SGND), U3.14 (SGND), U3.21 (EPAD); also elsewhere on the board
unnamed: C5.2, C6.2, R16.2, R17.1, U3.15 (FB)

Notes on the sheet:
For adjustable output version (AZ): ${19266913-80e0-457a-99b2-78e8e0500366:REFERENCE} = 1MΩ ${a9bf9950-5f5b-43e4-8b8c-8c8b79f444c7:REFERENCE} = 309kΩ (for 3.389V) ${abb20631-1ddd-48a5-a6d8-1b902ca094b4:REFERENCE}+${a4ade26b-8133-417f-a3c4-f707e58b4e1d:REFERENCE} = 66pF
For fixed 3.3V output version (NZ): ${19266913-80e0-457a-99b2-78e8e0500366:REFERENCE} = 0Ω ${a9bf9950-5f5b-43e4-8b8c-8c8b79f444c7:REFERENCE} = unfit ${abb20631-1ddd-48a5-a6d8-1b902ca094b4:REFERENCE}, ${a4ade26b-8133-417f-a3c4-f707e58b4e1d:REFERENCE} = unfit
Figure
Variation Aspect: ${61002a8a-6b88-406b-8c99-a0cdff0f1a3f:Var.Aspect}

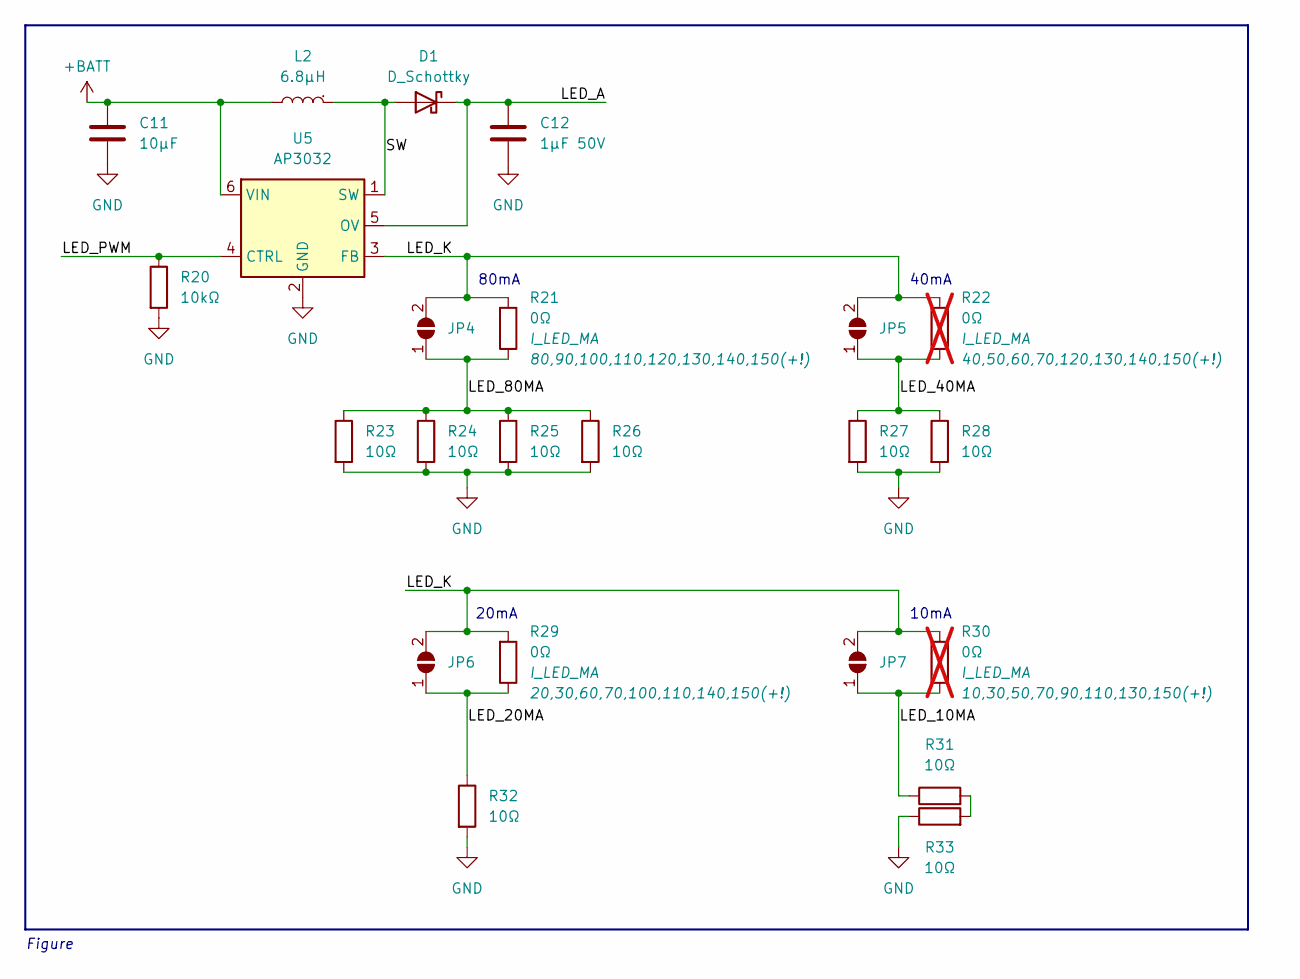
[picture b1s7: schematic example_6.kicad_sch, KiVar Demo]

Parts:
C11: 10µF; C_1206_3216Metric
C12: 1µF 50V; C_1206_3216Metric
D1: D_Schottky; D_0603_1608Metric
JP4, JP5, JP6, JP7: BT_CFG1_6; SolderJumper-2_P1.3mm_Open_RoundedPad1.0x1.5mm
L2: 6.8µH; L_Wuerth_MAPI-3020
R20: 10kΩ; R_0402_1005Metric
R21, R29: 0Ω; R_0402_1005Metric
R22, R30: 0Ω; R_0402_1005Metric; not fitted
R23, R24, R25, R26, R27, R28, R31, R32, R33: 10Ω; R_0402_1005Metric
U5: AP3032; SOT-23-6

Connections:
+BATT: C11.1, L2.2, U5.6 (VIN); also elsewhere on the board
/Example 6: Maximum LED Backlight Drive Current Selection/LED_10MA: JP7.1 (A), R30.1, R31.1
/Example 6: Maximum LED Backlight Drive Current Selection/LED_20MA: JP6.1 (A), R29.1, R32.1
/Example 6: Maximum LED Backlight Drive Current Selection/LED_40MA: JP5.1 (A), R22.1, R27.1, R28.1
/Example 6: Maximum LED Backlight Drive Current Selection/LED_80MA: JP4.1 (A), R21.1, R23.1, R24.1, R25.1, R26.1
/Example 6: Maximum LED Backlight Drive Current Selection/LED_A: C12.1, D1.1 (K), U5.5 (OV)
/Example 6: Maximum LED Backlight Drive Current Selection/LED_K: JP4.2 (B), JP5.2 (B), JP6.2 (B), JP7.2 (B), R21.2, R22.2, R29.2, R30.2, U5.3 (FB)
/Example 6: Maximum LED Backlight Drive Current Selection/LED_PWM: R20.1, U5.4 (CTRL)
/Example 6: Maximum LED Backlight Drive Current Selection/SW: D1.2 (A), L2.1, U5.1 (SW)
GND: C11.2, C12.2, R20.2, R23.2, R24.2, R25.2, R26.2, R27.2, R28.2, R32.2, R33.1, U5.2 (GND); also elsewhere on the board
unnamed: R31.2, R33.2

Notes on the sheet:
Figure
20mA
40mA
10mA
80mA

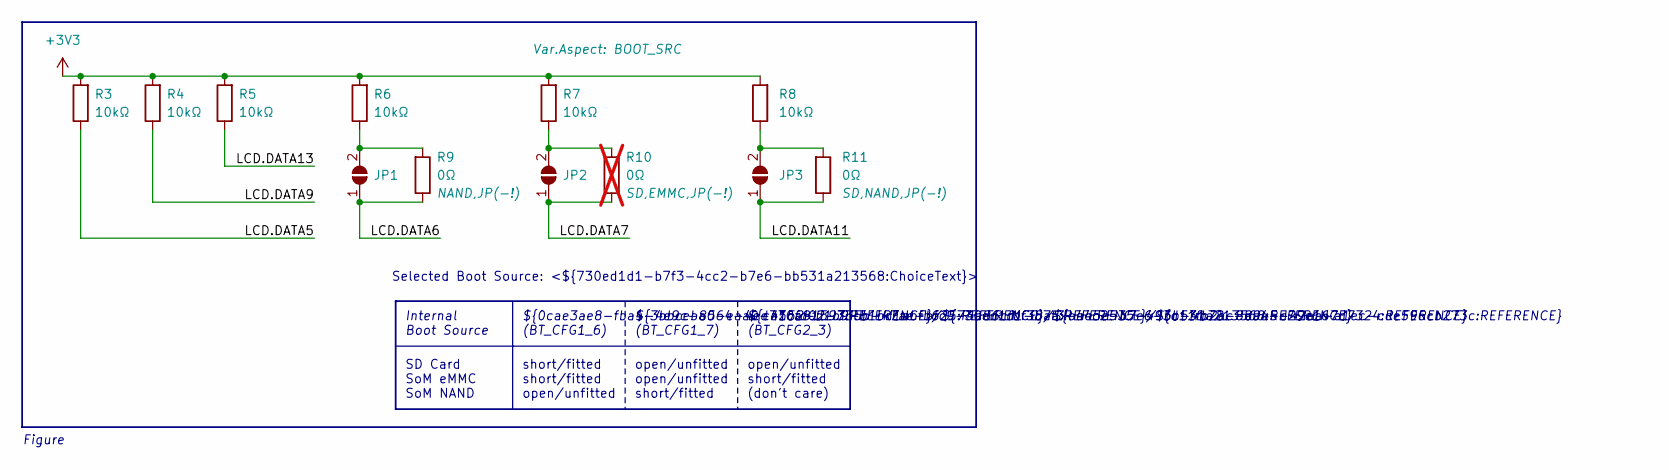
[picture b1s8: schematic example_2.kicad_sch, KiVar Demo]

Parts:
JP1: BT_CFG1_6; SolderJumper-2_P1.3mm_Open_RoundedPad1.0x1.5mm
JP2: BT_CFG1_7; SolderJumper-2_P1.3mm_Open_RoundedPad1.0x1.5mm
JP3: BT_CFG2_3; SolderJumper-2_P1.3mm_Open_RoundedPad1.0x1.5mm
R3, R4, R5, R6, R7, R8: 10kΩ; R_0402_1005Metric
R9, R11: 0Ω; R_0402_1005Metric
R10: 0Ω; R_0402_1005Metric; not fitted

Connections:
+3V3: R3.2, R4.2, R5.2, R6.2, R7.2, R8.2; also elsewhere on the board
/Example 2: Boot Source Selection/LCD.DATA5: R3.1
/Example 2: Boot Source Selection/LCD.DATA6: JP1.1 (A), R9.1
/Example 2: Boot Source Selection/LCD.DATA7: JP2.1 (A), R10.1
/Example 2: Boot Source Selection/LCD.DATA9: R4.1
/Example 2: Boot Source Selection/LCD.DATA11: JP3.1 (A), R11.1
/Example 2: Boot Source Selection/LCD.DATA13: R5.1
unnamed: JP1.2 (B), R6.1, R9.2
unnamed: JP2.2 (B), R7.1, R10.2
unnamed: JP3.2 (B), R8.1, R11.2

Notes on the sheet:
Internal Boot Source
Figure
Selected Boot Source: <${730ed1d1-b7f3-4cc2-b7e6-bb531a213568:ChoiceText}>
open/unfitted open/unfitted short/fitted
SD Card SoM eMMC SoM NAND
${3bbceba0-eaa0-4152-b1b9-b1bd1abfb625:REFERENCE}/${ba45e535-493c-4b78-88ea-d29e167d7324:REFERENCE} (BT_CFG1_7)
${ca5cfd02-335b-47ae-bfc9-4a86cfbf38aa:REFERENCE}/${d11fb2ac-e945-42aa-a1ec-cde596cb273c:REFERENCE} (BT_CFG2_3)
short/fitted short/fitted open/unfitted
open/unfitted short/fitted (don't care)
${0cae3ae8-fba4-4e9c-8564-4ed770a81597:REFERENCE}/${730ed1d1-b7f3-4cc2-b7e6-bb531a213568:REFERENCE} (BT_CFG1_6)

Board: 2 copper layers, 66 parts (0 on the bottom side), 29 nets, no tracks yet.

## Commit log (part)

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2024-03-19 Change KiVar field names
    Major change. Your old rules will not be found anymore. You need to
    rename your fields:
    "KiVar.Rule" -> "Var"
    "KiVar.Rule.Aspect" -> "Var.Aspect"
2024-03-19 Fix error for all commands but "list"
2024-03-19 Allow usage/mixing of both single and double quote characters, fix quoted output
2024-03-22 Fix handling of aux rules when component's base rule has zero choices listed
2024-03-22 Fix sorting of error messages (and make sorting of changes output style-agnostic)
2024-04-04 Begin readme update
2024-04-04 Update README.md
    WIP, at line 127.
2024-04-15 Remove verify option (ambiguity check now done during DB building)
2024-04-16 Check choice ambiguity only for a valid data set
2024-04-16 Enhance action plugin description
2024-04-16 Enable action plugin toolbar button by default
2024-04-16 Use shorter and nicer help URL
2024-04-16 Increase internal dev version number
2024-04-21 Change help URL and forwarding to be able to link to other doc sections, too
2024-05-08 Restyle icons
2024-05-08 Change PCM icon as well
2024-05-08 Add migration info (link not yet valid), change plugin/CLI/backend file names
2024-05-08 Fix import
2024-05-08 Add package generator scripts
    Ref #40
2024-05-08 Add PyPI package metadata info and package init file
2024-05-08 Create PyPI and PCM packages and plugin archive from a single release script
2024-05-08 Add more ignore patterns
2024-05-12 Add SVG test image
2024-05-12 Edit SVG test image
2024-05-12 Add differently scaled SVGs
2024-05-12 Add x2 scaled SVG
2024-05-13 Fix import (revert)
2024-05-14 Try to import from local file or module, then from same package
2024-05-14 Todo note about cleaning up the import mess
2024-05-14 Add shebang for CLI
2024-05-15 Make use of new 0.2.0 features in demo project, use different expression types
2024-05-15 Add new SVG example figures
2024-05-16 Add SVG "screenshots" of plugin
2024-05-16 Scale screenshots
    Scale in Inkscape: 1.6
2024-05-16 Resize again
2024-05-16 Scale again (both screenshots)
2024-05-17 Add some outlines to original icon
2024-05-17 Add some icon shape outlines (previous commit used wrong file)
2024-05-17 Update plugin screenshots and 3D images
    Selected choices need to be adapted in the doc text.
2024-05-21 Update gitignore
2024-05-21 Add expression processing figure
2024-05-22 Remove legacy rules from PCB file
2024-05-22 Link to migration guide if legacy rules are found (besides valid ones)
    Ref #65
2024-05-24 Match error messages with terms used in documentation (for 0.2.0)
2024-05-28 Remove obsolete images
2024-05-29 Finalize 0.2.0 preparations, add PyPI readme
2024-05-30 Filter Value, Reference, Footprint fields when reading board data
2024-05-30 Legacy rule detector: Only count "KiVar.Rule" fields with non-empty content
2024-05-31 Disallow usage of forbidden target field names
2024-05-31 Rephrase todo note
2024-05-31 Document forbidden target field names
2024-05-31 Unify field name check code
2024-05-31 Output PCM package info for pasting into versions array of metadata.json
2024-05-31 Update PCM package description, link to specific release
2024-05-31 Increase version to 0.2.1
2024-05-31 Update description
2024-05-31 Release script: Fix download URL
2024-07-04 Add support for 'S' (solder paste) property
2024-07-06 Move migration guide to end, add new props, add examples in term defs
2024-07-07 Refine doc for new properties
2024-07-11 Allow overriding output PCB file, require verbose option for printing changes in dry-run mode
2024-07-11 Increase version
2024-07-11 For each aspect, add a "VarID" field in an essential component to create a board variant ID code
2024-07-12 Update 3D PCB views
2024-07-12 Demo: Switch 3D models
2024-07-13 Increase version number
2024-07-14 Clean up demo project fields a bit
2024-07-14 Allow Aux rules to add new Choices, too
    Issue #71
2024-07-17 Add a note about package independence
2024-07-19 Introduce "stand-in" choices (symbol "?") as an alternative to "default" choices
2024-07-19 Plugin: Scrollable variant selection panel, allow maximizing window
2024-07-20 Rename scopes: Base->Component, Aux->Field
2024-07-20 Reflect scope naming changes in doc, add migration sub-section for next release
2024-07-21 Doc refinements
2024-07-21 Plugin: Do not stretch drop-down boxes vertically
2024-07-21 Fix a bug regarding choice dict finalization
2024-07-21 Demo PCB: Fix grouping
2024-07-29 Fix display and scroll issues, fix dialog button arrangement on non-GTK platforms
2024-08-08 Fine-tune dialog element margins to match look of KiCad dialogs
2024-08-17 Demo project: Use Stand-In choices where useful
2024-08-17 Demo: Add another example, update PCB
2024-08-17 Update doc SVGs
2024-08-17 Refine doc figure creation instructions
2024-08-22 Do not crash with error when PCB input file name is missing
2024-08-22 Increase development version number
2024-08-22 Simply import * from backend
2024-08-22 Remove obsolete notes
2024-08-22 Do PCB modification after dialog is destroyed
2024-08-22 Update images and image creation instructions
2024-08-23 Use colored output for the CLI app, allow multiple queries for state command
2024-08-23 Fix default redirection to stderr for error messages
2024-08-23 Update doc images
2024-08-23 Example 7: Also switch solder paste
2024-08-23 Update PCB
2024-08-23 Swap page numbers
2024-08-25 Fix error reporting
2024-09-03 Fine-tune colors
2024-09-10 Add pcbnew version info to kivar CLI app
2024-09-10 Use "python3" instead of "python"
2024-09-10 Bugfix: Remove obsolete assignment not honoring dry_run state
2024-09-11 Get release version from backend
2024-09-13 Update documentation for upcoming 0.4.0 release
2024-09-13 Example 7: Add 2.5V choice, refine
2024-09-13 Refine dialog titles
2024-09-13 Refine/update error message texts
2024-09-13 Update demo project date
2024-09-14 Refine documentation
2024-09-14 Remove obsolete todo notes
2024-09-14 Update icon renders
2024-09-14 Update package description for PCM
2024-09-14 Update package description for PyPI
2024-09-14 Refine PCM description
2024-09-14 Add a few ideas for next releases
2024-09-16 Fix demo project for 0.4.0 re-release
2024-09-16 Fix CLI output in readme, update PCB 3D views for re-release
2024-09-24 Save and restore main and error window sizes
2024-09-24 Add keep_on_update, rename PCM metadata template file
2024-09-24 Increase version for upcoming release
2024-11-07 CLI: Fix missing compatibility problem message
2024-11-07 Plugin: Match capitalization style with KiCad
    Match with KiCad commit:
    https://gitlab.com/kicad/code/kicad/-/commit/92315162384f7f9081680b4e955640ab944af889
2024-11-08 Allow inheritance of solder paste clearance value (for KiCad 9)
2024-11-14 Improve processing speed and error reporting of ambiguity check
2024-11-15 Check for empty aspects that have no choices attached
2024-11-15 Improve ambiguity error reporting
2024-11-15 Unify passing the parent to dialog ctors
2024-11-16 Add table for KiCad release compatibility
2024-11-16 Settle version number for upcoming release
2025-03-29 Implement variant support in engine and GUI, restructure source tree
2025-03-29 Fix resize issues
2025-04-20 Basic coverage of 0.5.x series (mainly variants)
2025-04-21 Work around layout issues
2025-04-21 Pre-focus OK button
2025-04-21 Update plugin screenshots, change from SVG to PNG
2025-04-21 Remove todo notes
2025-04-22 Update doc info
2025-04-23 Use "unspecified" instead of "unset" (used in new GUI)
2025-04-23 Add a few more special characters (used in CLI) that trigger quoting
2025-04-23 CLI: Implement variant support for "list" command
2025-04-24 Add variant support for "state" command, prepare others
2025-04-24 Improve text about table/variant creation
2025-04-25 Add variant support to set command
2025-04-25 Shorten
2025-04-25 Add example variant definition table
2025-04-25 Implement variant support for check command
2025-04-25 Specify specific variants to switch between
2025-04-25 Doc: Update PCB and plugin images
2025-04-25 Use circle marker right of aspect name instead of bold font
2025-04-25 Avoid Unicode in source code
2025-04-25 Refine line break
2025-04-25 Add KiCad plugin entry code
2025-04-26 Refine doc
2025-04-26 Increase zoom a bit to avoid edge on top of rendered image
2025-04-27 Readme: Refine variants stuff
2025-04-27 CLI: Change active variant highlight text color
    Visual contrast depends on terminal emulator color scheme
2025-04-27 CLI: Use escape_str() for pre-quoted strings in messages
2025-04-27 Readme: Refine
2025-04-28 Reduce icon aliasing on different scale factors
    Manual says to keep the plugin icon at 24×24px, but automatic scaling of larger images seems to work just fine.
2025-04-28 Fix uncovered case when no PCB file name is provided yet
2025-04-28 Improve line wrapping
2025-04-29 Use BE, as preferred by wx
2025-04-29 Dynamically scale and cache plugin icon, improve modification marking, try to fix some MacOS issues
2025-04-29 Manually handling scroll wheel events on wxChoices has issues on MacOS, give up on redefining UX
2025-04-29 Change PCB stackup colors, re-render 3D views
2025-04-29 Refine icon artwork
2025-04-29 Update icon PNG renders
2025-04-30 Add some thanks
2025-04-30 Increase dev version
2025-04-30 Update date in demo project schematic and PCB
2025-05-03 Demo: Switch state to specific variant
2025-05-03 Rename .kivar.csv to .kivar_vdt.csv
2025-05-03 Use consistent naming for VDTs
2025-05-03 Explain Python distribution issues on non-Linux
2025-05-03 Update plugin screenshots with aligned "modified" markers
2025-05-03 Remove obsolete to-do notes
2025-05-03 Add tooltip to "modified" markers
2025-05-03 Change .kivar.csv extension to .kivar_vdt.csv (aligns better with .kicad_* extensions, refers to actual file purpose)
2025-05-03 Fix PEP-517 deprecation issue
2025-05-03 Update readme texts for project, PyPI, PCM
2025-05-03 Remove obsolete comments and code
2025-05-03 Bump version to 0.5.0
2025-05-03 Small last changes to readme files
2025-05-03 Change status from testing to stable
2025-05-04 Change download URL
2025-05-08 Fix nested quoting in f-strings (for Python < 3.12)
    Fixes #88
2025-05-08 Bump version (only used for CLI app post-release)
2025-05-12 Readme: Remove leftovers from editing
2025-05-23 Allow for some flexibility in the kivar field base (allow projects to stray from "Var" according to taste). Supports Var, Variant, Config, or Build.
2025-05-23 Give field options priority based on order
2025-05-25 Allow custom keywords for Var and Aspect
2025-06-13 Mention keyword customization in documentation
2025-06-14 Settle version for release
2025-08-10 Improved error statements when checking aspect value and property assignment
2025-08-10 inconsistent for/of usage
2025-09-05 Fix mistake in Readme
2025-09-21 Refine error messages value escaping and wording
2025-09-21 Bump version to 0.5.2
2025-11-26 Add GitHub action to test CLI app install on macOS
2025-11-26 Add push trigger
2025-11-26 Action: Try again
2025-11-26 Action: List KiCad dir content for debugging location of Python modules
2025-11-26 Add test with demo project
2025-11-26 Test alternate call syntax
2025-11-27 Try installation with --user option, see where it gets installed
2025-11-27 Further testing
2025-11-28 Try symlinking into PATH location
2025-11-28 Add bin dir
2025-11-28 Improve and update CLI app installation instructions, per OS
2025-11-30 Small doc changes
2025-11-30 Add .exe suffix for Windows
2025-11-30 Small refinements in the doc, emphasize tips for starters
2025-11-30 Remove macOS CLI app installation test workflow
2025-11-30 Improve CLI app installation instructions (#98)
2026-03-12 Fix a dialog text wrapping issue, enhance dialog text to help new users get started, add button to edit VDT when table-related errors are found
2026-03-12 Remove obsolete comment
2026-03-12 Refine documentation, emphasize multi-scope concept
2026-03-12 Sync readme files, do not capitalize keywords in intro text
2026-03-12 Bump version
2026-03-21 Fix KiCad 10 compatibility issue Resolves #103
2026-03-21 Fix doc: KiCad 10 requires at least KiVar v0.5.4
